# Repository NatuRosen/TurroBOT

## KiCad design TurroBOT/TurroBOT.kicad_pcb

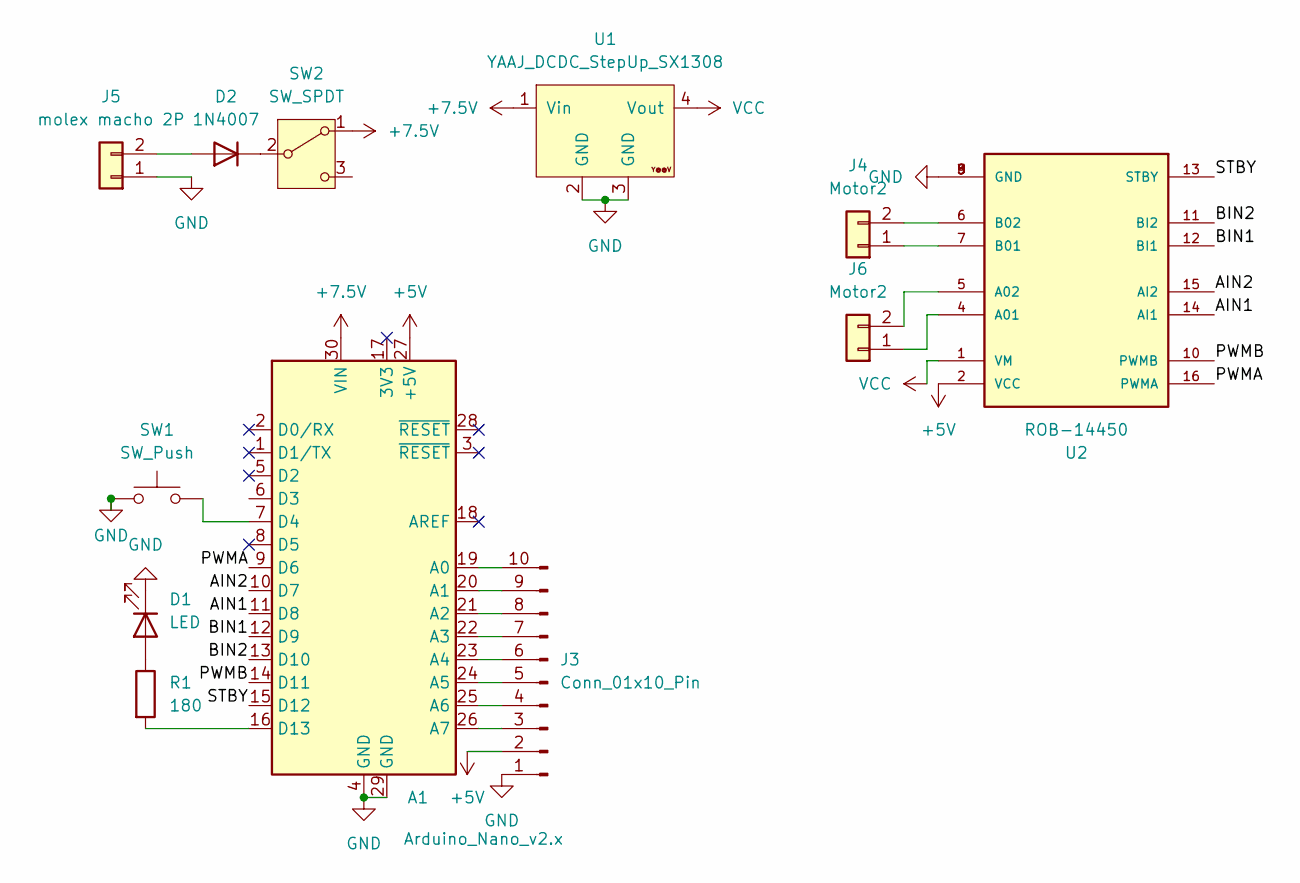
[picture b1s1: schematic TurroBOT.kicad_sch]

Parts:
A1: Arduino_Nano_v2.x; Arduino_Nano
D1: LED; LED_D3.0mm
D2: 1N4007; D_DO-41_SOD81_P10.16mm_Horizontal
J3: Conn_01x10_Pin; PinHeader_1x10_P2.00mm_Vertical
J4, J6: Motor2; Molex_KK-254_AE-6410-02A_1x02_P2.54mm_Vertical
J5: molex macho 2P; Molex_KK-254_AE-6410-02A_1x02_P2.54mm_Vertical
R1: 180; R_1206_3216Metric
SW1: SW_Push; SW_PUSH_6mm
SW2: SW_SPDT; SW_Slide_SPDT_Straight_CK_OS102011MS2Q
U1: YAAJ_DCDC_StepUp_SX1308
U2: ROB-14450; MODULE_ROB-14450; PARTREV 11-13-17

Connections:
+5V: A1.27 (+5V), J3.2, U2.2 (VCC)
+7.5V: A1.30 (VIN), SW2.1 (A), U1.1 (Vin)
/AIN1: A1.11 (D8), U2.14 (AI1)
/AIN2: A1.10 (D7), U2.15 (AI2)
/BIN1: A1.12 (D9), U2.12 (BI1)
/BIN2: A1.13 (D10), U2.11 (BI2)
/PWMA: A1.9 (D6), U2.16 (PWMA)
/PWMB: A1.14 (D11), U2.10 (PWMB)
/STBY: A1.15 (D12), U2.13 (STBY)
GND: A1.4 (GND), A1.29 (GND), D1.1 (K), J3.1, J5.1, SW1.1, U1.2 (GND), U1.3 (GND), U2.3 (GND), U2.8 (GND), U2.9 (GND)
unnamed: A1.19 (A0), J3.10
unnamed: A1.20 (A1), J3.9
unnamed: A1.21 (A2), J3.8
unnamed: A1.22 (A3), J3.7
unnamed: A1.23 (A4), J3.6
unnamed: A1.24 (A5), J3.5
unnamed: A1.25 (A6), J3.4
unnamed: A1.26 (A7), J3.3
unnamed: A1.7 (D4), SW1.2
unnamed: A1.16 (D13), R1.2
unnamed: D1.2 (A), R1.1
unnamed: D2.2 (A), J5.2
unnamed: D2.1 (K), SW2.2 (B)
unnamed: J4.1, U2.7 (B01)
unnamed: J4.2, U2.6 (B02)
unnamed: J6.1, U2.4 (A01)
unnamed: J6.2, U2.5 (A02)
VCC: U1.4 (Vout), U2.1 (VM)

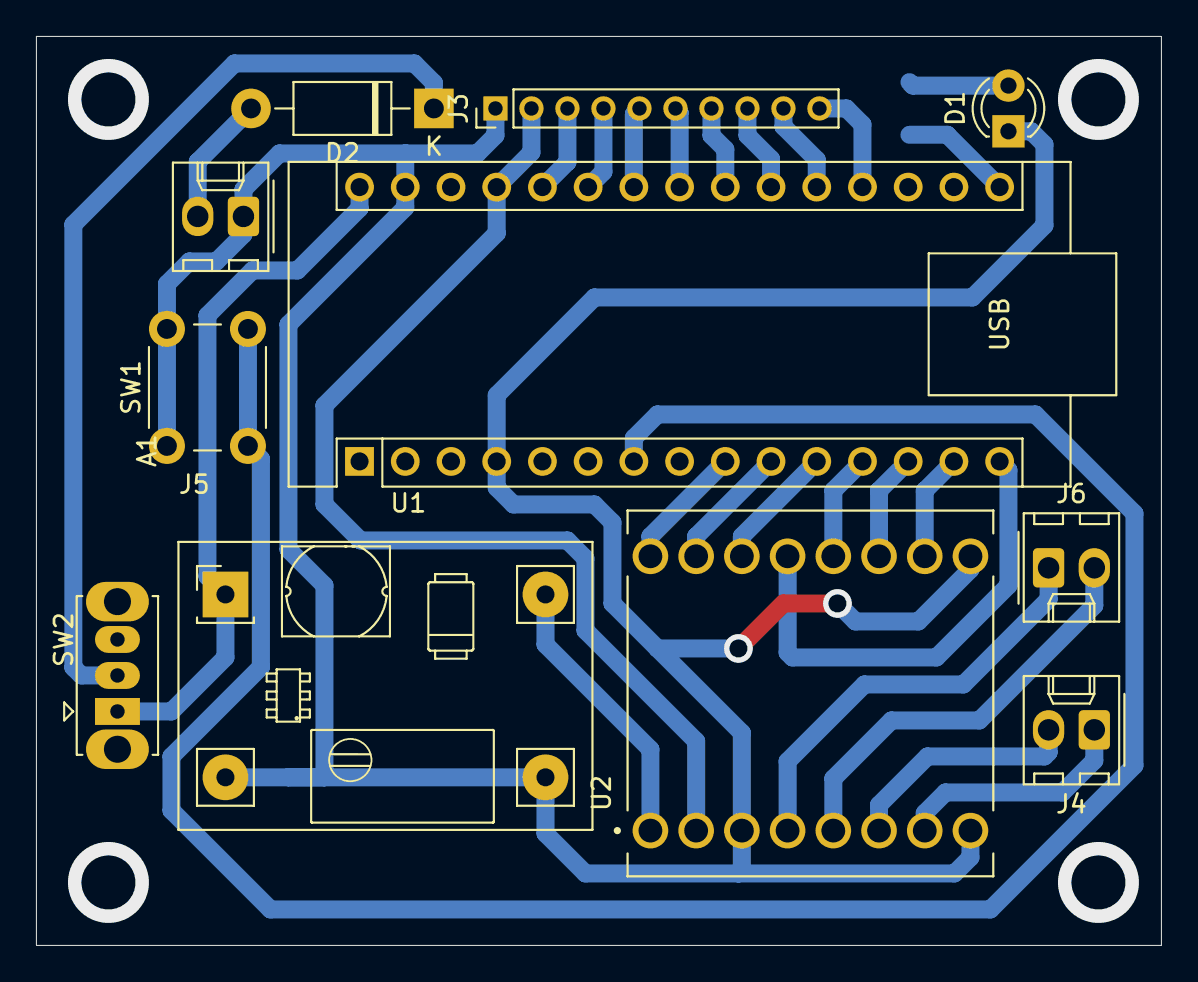
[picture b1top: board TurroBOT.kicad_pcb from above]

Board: 2 copper layers, 62.5 x 50.5 mm, 12 parts (1 on the bottom side), 28 nets.

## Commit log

2024-12-05 esq terminado
2024-12-05 casi todas las footprints cargadas
2024-12-05 falta solo footprint del switch
2024-12-06 todo listo
2024-12-06 lista la placa, step y pdf
2024-12-06 arreglado detallito del esq
